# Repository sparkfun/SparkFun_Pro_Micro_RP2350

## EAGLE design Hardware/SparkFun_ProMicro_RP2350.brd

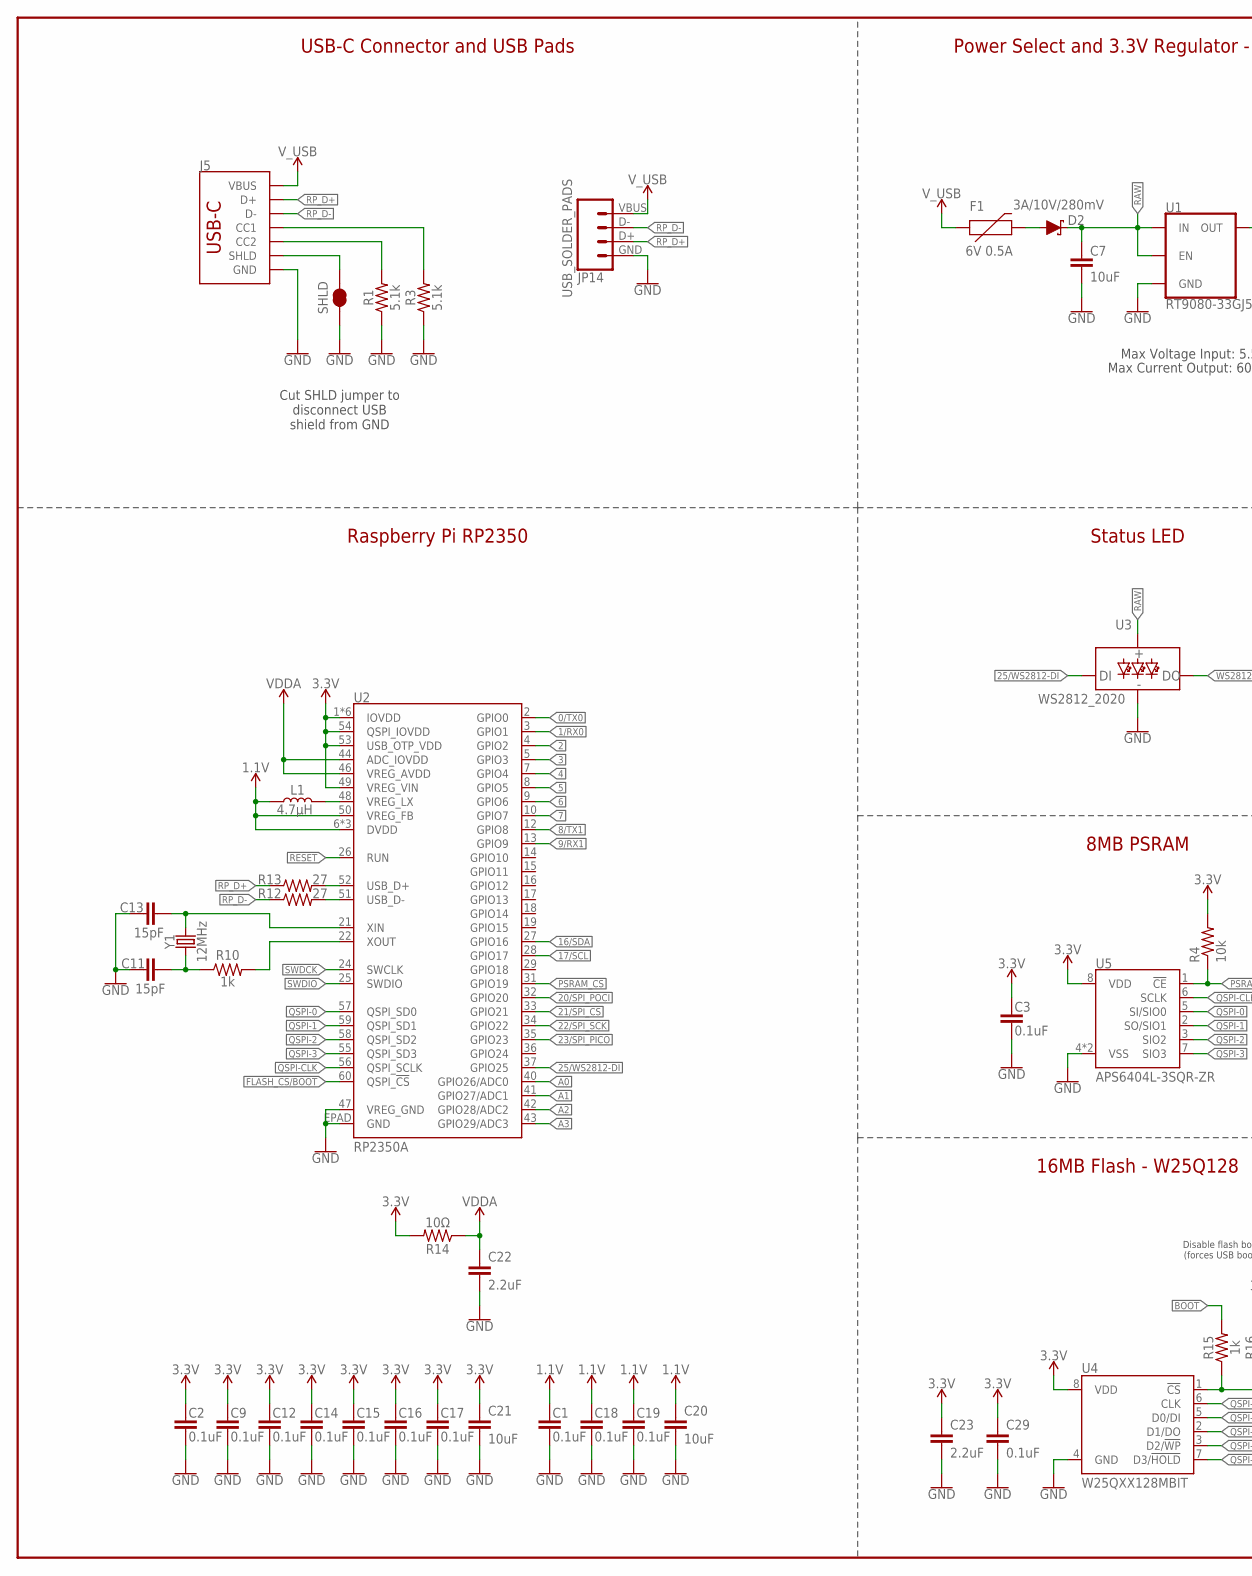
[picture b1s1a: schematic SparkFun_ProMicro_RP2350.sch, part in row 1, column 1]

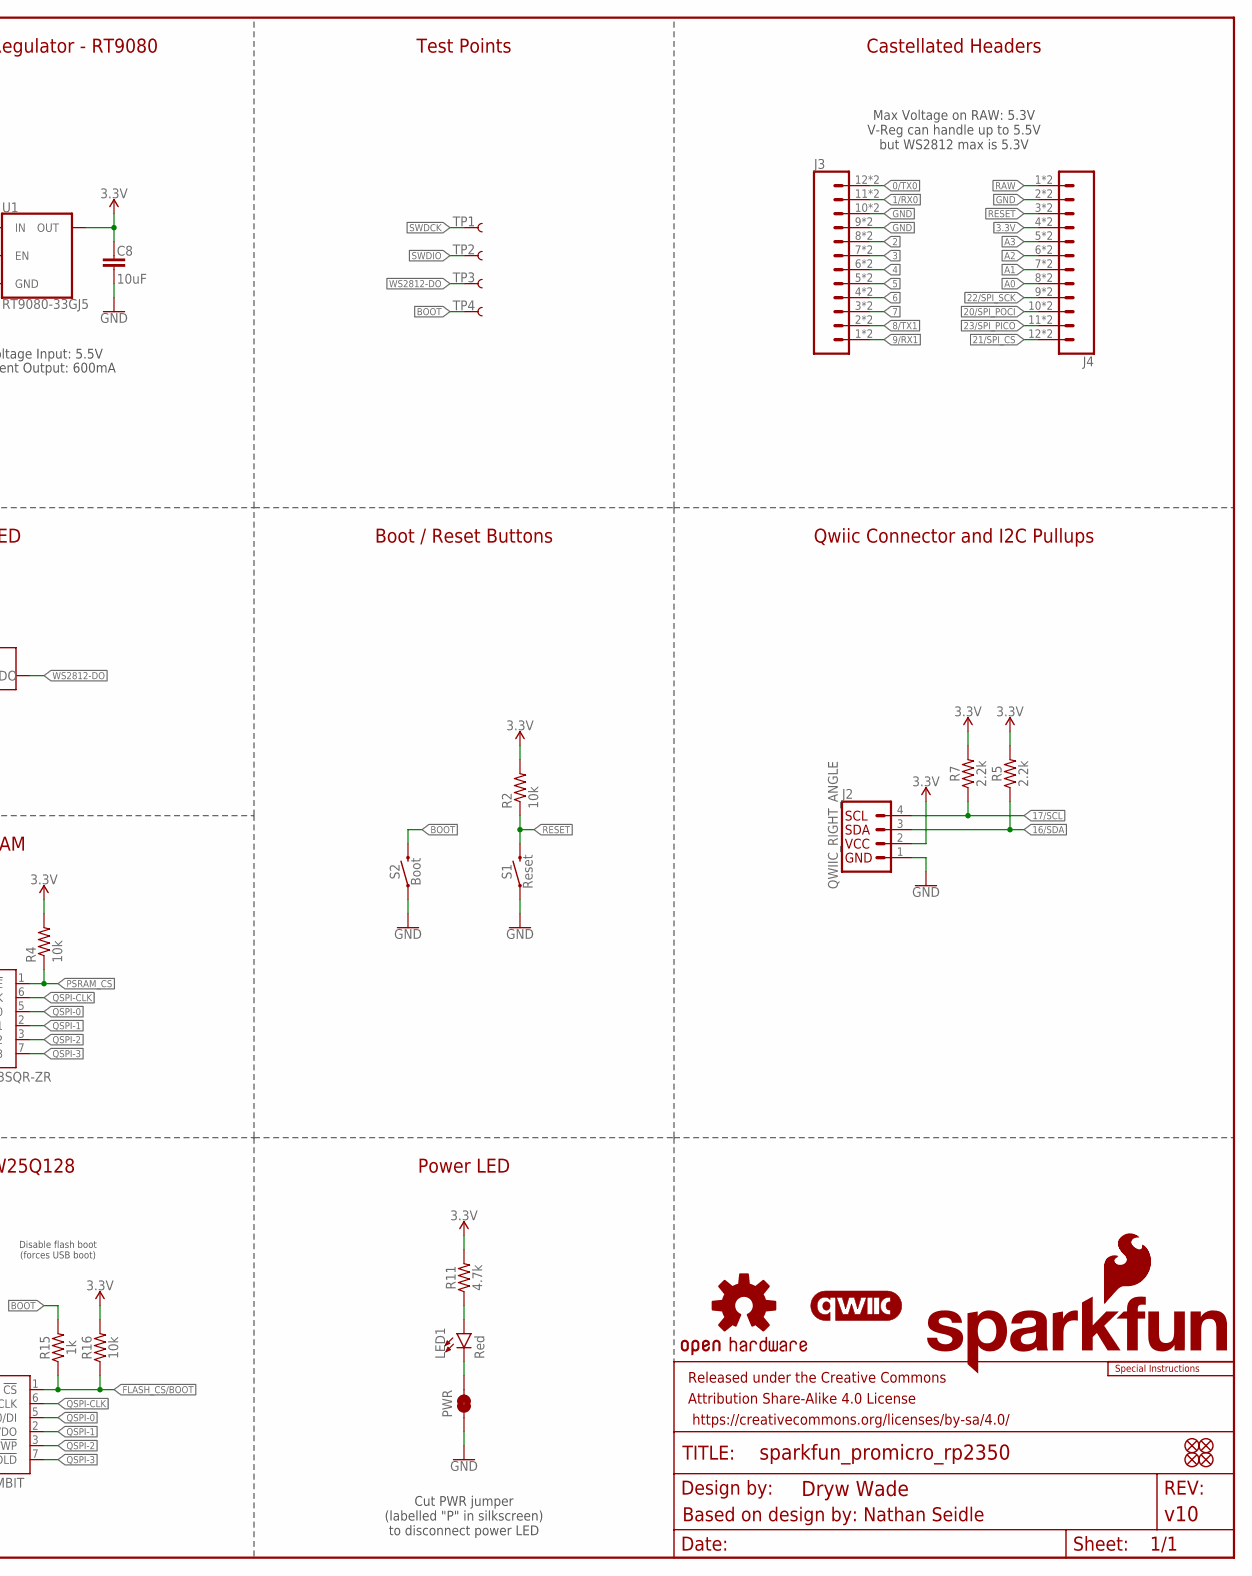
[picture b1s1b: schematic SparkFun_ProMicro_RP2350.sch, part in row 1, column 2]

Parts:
C1, C2, C3, C9, C12, C14, C15, C16, C17, C18, C19, C29: 0.1uF; 0402-TIGHT
C7, C8, C20, C21: 10uF; 0402-TIGHT
C11, C13: 15pF; 0402-TIGHT
C22, C23: 2.2uF; 0402-TIGHT
D2: 3A/10V/280mV; SOD-323
F1: 6V 0.5A; 0805
FRAME2: FRAME-LEDGER; CREATIVE_COMMONS
J2: QWIIC_RIGHT_ANGLE; JST04_1MM_RA
J3, J4: CONN_12CASTELLATED; 1X12_CASTELLATED
J5: USB Female Type C Connector; USB-C-16P_4LAYER-PADS
JP1, JP2, JP3, JP4: FIDUCIAL1X2; FIDUCIAL-1X2
JP14: USB_SOLDER_PADS; USB-SOLDER-PADS
L1: 4.7μH; 1008(2520)
LED1: Red; LED-0603
LOGO1: SFE_LOGO_NAME_FLAME.1_INCH; SFE_LOGO_NAME_FLAME_.1
LOGO3: QWIIC_LOGO_6MM; QWIIC_6MM
LOGO4: SFE_LOGO_FLAME.1_INCH; SFE_LOGO_FLAME_.1
LOGO5: SPECIAL_INSTRUCTIONS-ORDERING; ORDERING_INSTRUCTIONS
PWR: JUMPER-SMT_2_NC_TRACE_SILK; SMT-JUMPER_2_NC_TRACE_SILK
R1, R3: 5.1k; 0402-TIGHT
R2, R4, R16: 10k; 0402-TIGHT
R5, R7: 2.2k; 0402-TIGHT
R10, R15: 1k; 0402-TIGHT
R11: 4.7k; 0402-TIGHT
R12, R13: 27; 0402-TIGHT
R14: 10Ω; 0402-TIGHT
S1: Reset; TACTILE_SWITCH_SMD_4.6X2.8MM
S2: Boot; TACTILE_SWITCH_SMD_4.6X2.8MM
SHLD: JUMPER-SMT_2_NC_TRACE_SILK; SMT-JUMPER_2_NC_TRACE_SILK
TP1, TP2, TP3, TP4: TEST-POINT3X5; PAD.03X.05
U1: RT9080-33GJ5; SOT23-5
U2: RP2350A
U3: WS2812_2020; WS2812-2020
U4: W25QXX128MBIT; WSON-8-6X5-SKINNY_CENTERPAD
U5: APS6404L-3SQR-ZR
U$3: OSHW-LOGOMINI; OSHW-LOGO-MINI
Y1: 12MHz; CRYSTAL-SMD-2X2.5MM

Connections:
0/TX0: J3.12, J3.12B (12), U2.2 (GPIO0)
1.1V: C1.1, C18.1, C19.1, C20.1, L1.1, U2.6 (DVDD), U2.23 (DVDD), U2.39 (DVDD), U2.50 (VREG_FB)
1/RX0: J3.11, J3.11B (11), U2.3 (GPIO1)
2: J3.8, J3.8B (8), U2.4 (GPIO2)
3: J3.7, J3.7B (7), U2.5 (GPIO3)
3.3V: C2.1, C3.1, C8.2, C9.1, C12.1, C14.1, C15.1, C16.1, C17.1, C21.1, C23.1, C29.1, J2.2, J4.4, J4.4B (4), R2.2, R4.2, R5.2, R7.2, R11.2, R14.2, R16.2, U1.5 (OUT), U2.1 (IOVDD), U2.11 (IOVDD), U2.20 (IOVDD), U2.30 (IOVDD), U2.38 (IOVDD), U2.45 (IOVDD), U2.49 (VREG_VIN), U2.53 (USB_OTP_VDD), U2.54 (QSPI_IOVDD), U4.8 (VDD), U5.8 (VDD)
4: J3.6, J3.6B (6), U2.7 (GPIO4)
5: J3.5, J3.5B (5), U2.8 (GPIO5)
6: J3.4, J3.4B (4), U2.9 (GPIO6)
7: J3.3, J3.3B (3), U2.10 (GPIO7)
8/TX1: J3.2, J3.2B (2), U2.12 (GPIO8)
9/RX1: J3.1, J3.1B (1), U2.13 (GPIO9)
16/SDA: J2.3, R5.1, U2.27 (GPIO16)
17/SCL: J2.4, R7.1, U2.28 (GPIO17)
20/SPI_POCI: J4.10, J4.10B (10), U2.32 (GPIO20)
21/SPI_!CS!: J4.12, J4.12B (12), U2.33 (GPIO21)
22/SPI_SCK: J4.9, J4.9B (9), U2.34 (GPIO22)
23/SPI_PICO: J4.11, J4.11B (11), U2.35 (GPIO23)
25/WS2812-DI: U2.37 (GPIO25), U3.DI
!RESET!: J4.3, J4.3B (3), R2.1, S1.3 (2), S1.4 (2), U2.26 (RUN)
A0: J4.8, J4.8B (8), U2.40 (GPIO26/ADC0)
A1: J4.7, J4.7B (7), U2.41 (GPIO27/ADC1)
A2: J4.6, J4.6B (6), U2.42 (GPIO28/ADC2)
A3: J4.5, J4.5B (5), U2.43 (GPIO29/ADC3)
BOOT: R15.2, S2.3 (2), S2.4 (2), TP4.1
FLASH_!CS!/BOOT: R15.1, R16.1, U2.60 (QSPI_!CS!), U4.1 (!CS!)
GND: C1.2, C2.2, C3.2, C7.1, C8.1, C9.2, C11.1, C12.2, C13.1, C14.2, C15.2, C16.2, C17.2, C18.2, C19.2, C20.2, C21.2, C22.2, C23.2, C29.2, J2.1, J3.9, J3.9B (9), J3.10, J3.10B (10), J4.2, J4.2B (2), J5.GND, J5.GND2 (GND), JP14.GND (4), PWR.1, R1.1, R3.1, S1.1, S1.2 (1), S2.1, S2.2 (1), SHLD.2, U1.2 (GND), U2.47 (VREG_GND), U2.EPAD (GND), U3.GND, U4.4 (GND), U5.4 (VSS), U5.9 (VSS)
unnamed: L1.2, U2.48 (VREG_LX)
unnamed: LED1.C, PWR.2
unnamed: J5.A5 (CC1), R3.2
unnamed: J5.B5 (CC2), R1.2
unnamed: LED1.A, R11.1
PSRAM_!CS!: R4.1, U2.31 (GPIO19), U5.1 (!CE!)
QSPI-0: U2.57 (QSPI_SD0), U4.5 (D0/DI), U5.5 (SI/SIO0)
QSPI-1: U2.59 (QSPI_SD1), U4.2 (D1/DO), U5.2 (SO/SIO1)
QSPI-2: U2.58 (QSPI_SD2), U4.3 (D2/!WP!), U5.3 (SIO2)
QSPI-3: U2.55 (QSPI_SD3), U4.7 (D3/!HOLD!), U5.7 (SIO3)
QSPI-CLK: U2.56 (QSPI_SCLK), U4.6 (CLK), U5.6 (SCLK)
RAW: C7.2, D2.C, J4.1, J4.1B (1), U1.1 (IN), U1.3 (EN), U3.VCC
RP_D1+: R13.2, U2.52 (USB_D+)
RP_D1-: R12.2, U2.51 (USB_D-)
RP_D+: J5.A6 (D+), J5.B6 (D+), JP14.D+ (3), R13.1
RP_D-: J5.A7 (D-), J5.B7 (D-), JP14.D- (2), R12.1
SHLD: J5.SHLD1 (SHLD), J5.SHLD2 (SHLD), J5.SHLD3 (SHLD), J5.SHLD4 (SHLD), SHLD.1
SWDCK: TP1.1, U2.24 (SWCLK)
SWDIO: TP2.1, U2.25 (SWDIO)
USB_RAW: D2.A, F1.2
VDDA: C22.1, R14.1, U2.44 (ADC_IOVDD), U2.46 (VREG_AVDD)
V_USB: F1.1, J5.VBUS1 (VBUS), J5.VBUS2 (VBUS), JP14.VBUS (1)
WS2812-DO: TP3.1, U3.DO
X1A: R10.2, U2.22 (XOUT)
X1B: C11.2, R10.1, Y1.P1 (1)
X2: C13.2, U2.21 (XIN), Y1.P3 (2)

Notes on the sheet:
Max Voltage Input: 5.5V
Max Current Output: 600mA
Raspberry Pi RP2350
16MB Flash - W25Q128
Disable flash boot (forces USB boot)
Status LED
Power Select and 3.3V Regulator - RT9080
USB-C Connector and USB Pads
Castellated Headers
Boot / Reset Buttons
Max Voltage on RAW: 5.3V V-Reg can handle up to 5.5V but WS2812 max is 5.3V
Based on design by: Nathan Seidle
Cut SHLD jumper to disconnect USB shield from GND
Cut PWR jumper (labelled "P" in silkscreen) to disconnect power LED
Power LED
Qwiic Connector and I2C Pullups
Test Points
8MB PSRAM

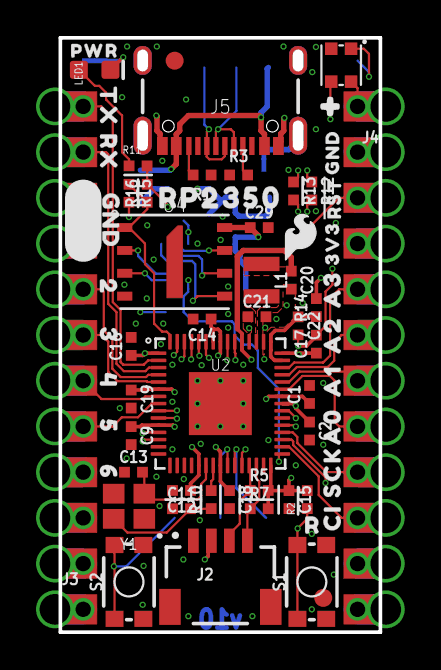
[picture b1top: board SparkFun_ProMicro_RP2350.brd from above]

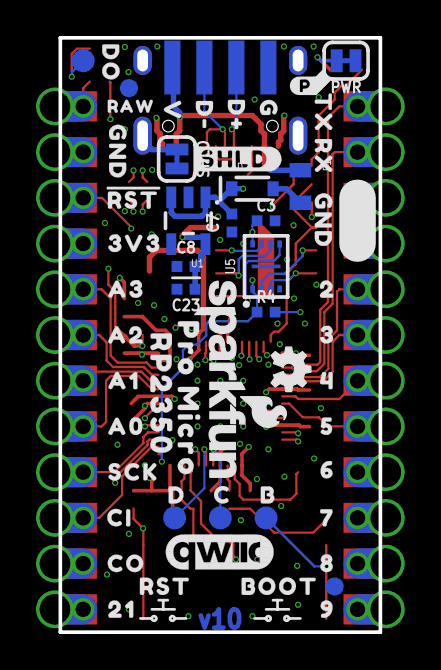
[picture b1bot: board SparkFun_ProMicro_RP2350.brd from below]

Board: 4 copper layers, 17.8 x 33.0 mm, 124 parts (58 on the bottom side), 53 nets.

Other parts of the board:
U$1, U$11: A00
U$2: GND_0
U$4: PRO_MICRO0
U$5: #0
U$6: 70
U$7: 81
U$8: 92
U$9, U$64: CI4
U$10, U$67: SCK3
U$12, U$20: A10
U$13, U$33: A21
U$14, U$39: A32
U$15, U$22, U$74: GND2
U$16: 3V3_0
U$17: RAW0
U$18: C0
U$19, U$76: TX0
U$21, U$75: RX1
U$23, U$53: 20
U$24, U$54: 31
U$25, U$55: 42
U$26, U$56: 53
U$27, U$57: 64
U$28: D#1
U$29: D#2
U$30: G0
U$31: V3
U$32: 210
U$34: #RST#0
U$35: D1
U$36: #P#0
U$37: R0
U$38: B0
U$40: DO0
U$41: BOOT0
U$42, U$45: RP23500
U$43: #SHLD#0
U$44: RST0
U$66: CO5
U$68: #RST#1
U$69: 3V30
U$73: PWR0

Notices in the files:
parts and their libraries:
SparkFun-Aesthetics: Licensing: CC v3.0 Share-Alike You are welcome to use this library for commercial purposes.
SparkFun-Aesthetics: Released under the Creative Commons Attribution Share-Alike 4.0 License
SparkFun-Aesthetics: https://creativecommons.org/licenses/by-sa/4.0
